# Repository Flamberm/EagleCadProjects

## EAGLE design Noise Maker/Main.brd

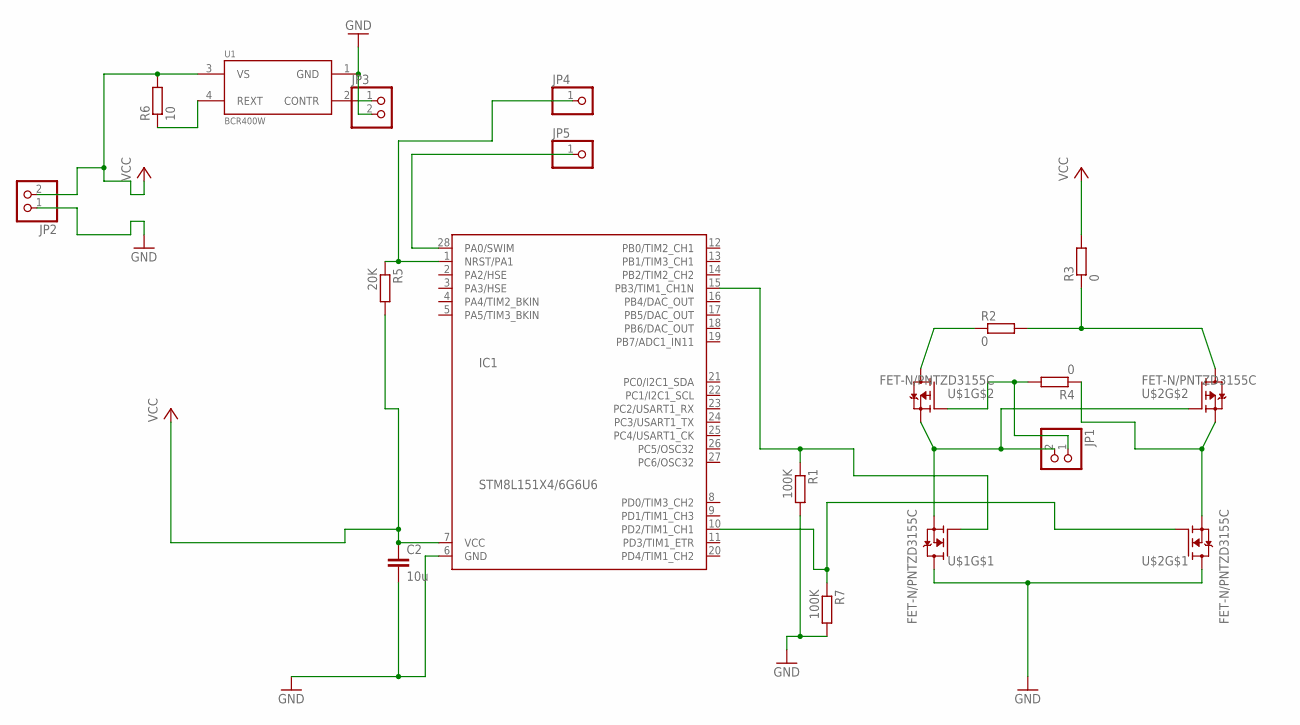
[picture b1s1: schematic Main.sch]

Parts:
C2: 10u; C0805
IC1: STM8L151X4/6G6U6; QFN28
JP1, JP2, JP3: PINHD-1X2; 1X02
JP4, JP5: PINHD-1X1; 1X01
R1, R7: 100K; R0805
R2, R3, R4: 0; R0805
R5: 20K; R0805
R6: 10; R0805
U1: BCR400W; SOT130P210X100-4N
U$1, U$2: FET-N/PNTZD3155C; SOT-563

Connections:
GND: C2.2, IC1.6 (GND), JP2.1, JP3.2, R1.2, R7.2, U1.1 (GND), U$1.6 (D), U$2.6 (D)
unnamed: R6.1, U1.4 (REXT)
unnamed: IC1.28 (PA0/SWIM), JP5.1
unnamed: IC1.1 (NRST/PA1), JP4.1, R5.1
unnamed: JP3.1, U1.2 (CONTR)
unnamed: R4.1, U$2.1 (S), U$2.4 (S)
unnamed: JP1.2, U$1.1 (S), U$1.4 (S), U$2.5 (G)
unnamed: IC1.10 (PD2/TIM1_CH1), R7.1, U$2.2 (G)
unnamed: R2.1, U$1.3 (D)
unnamed: R2.2, R3.1, U$2.3 (D)
unnamed: JP1.1, R4.2, U$1.5 (G)
unnamed: IC1.15 (PB3/TIM1_CH1N), R1.1, U$1.2 (G)
VCC: C2.1, IC1.7 (VCC), JP2.2, R3.2, R5.2, R6.2, U1.3 (VS)

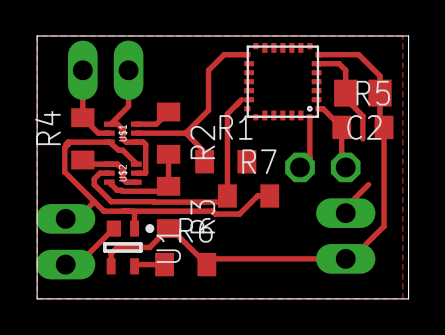
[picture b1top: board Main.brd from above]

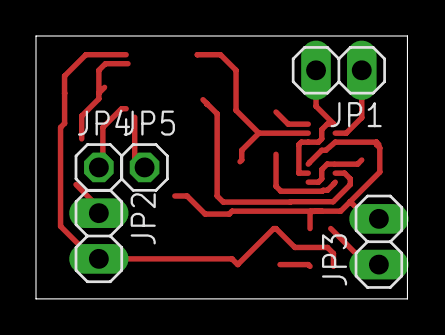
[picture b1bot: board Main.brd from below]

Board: 2 copper layers, 20.6 x 14.6 mm, 17 parts (5 on the bottom side), 13 nets.

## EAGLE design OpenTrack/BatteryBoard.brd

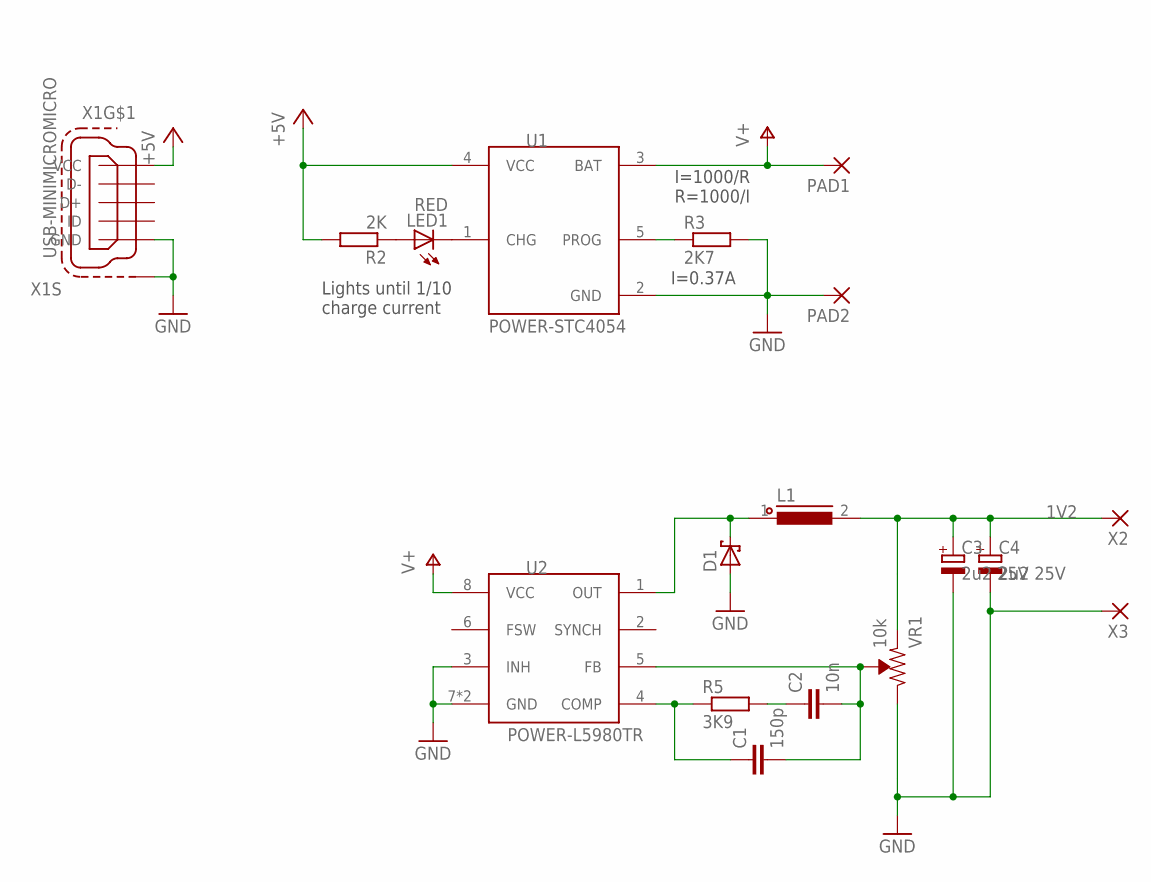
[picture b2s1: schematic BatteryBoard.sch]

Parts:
C1: 150p; CAP0805
C2: 10n; CAP0805
C3, C4: 2u2 25V; CAPMP3317X180
D1: DIODE-SH_SMA; DO214AC
L1: INDUCTORNL4532; INDM4232X320
LED1: RED; LED1206
PAD1, PAD2: WIREPAD-SMD2; PAD-1.27X2.54
R2: 2K; RESC2012X50
R3: 2K7; RESC2012X50
R5: 3K9; RESC2012X50
U1: POWER-STC4054; SOT95P280X145-5
U2: POWER-L5980TR; QFPN8
VR1: 10k; TRIMPOT-SMD-TC33X
X1: USB-MINIMICROMICRO; USB-B-MICRO-SMD
X2, X3: WIREPAD-SMD2; PAD-1.27X2.54

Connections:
1V2: C3.1 (+), C4.1 (+), L1.2, VR1.3 (CCW), X2.P$1
+5V: R2.2, U1.4 (VCC), X1.VBUS (VCC)
GND: C3.2 (-), C4.2 (-), D1.A, PAD2.P$1, R3.2, U1.2 (GND), U2.3 (INH), U2.7 (GND), U2.EXP (GND), VR1.1 (CW), X1.GND, X1.SHIELD1 (S1), X1.SHIELD2 (S1), X1.SHIELD3 (S1), X3.P$1
unnamed: LED1.C, U1.1 (CHG)
unnamed: LED1.A, R2.1
unnamed: D1.C, L1.1, U2.1 (OUT)
unnamed: R3.1, U1.5 (PROG)
unnamed: C1.2, C2.2, U2.5 (FB), VR1.2 (WIPER)
unnamed: C2.1, R5.2
unnamed: C1.1, R5.1, U2.4 (COMP)
V+: PAD1.P$1, U1.3 (BAT), U2.8 (VCC)

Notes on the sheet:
I=1000/R R=1000/I
I=0.37A
Lights until 1/10 charge current

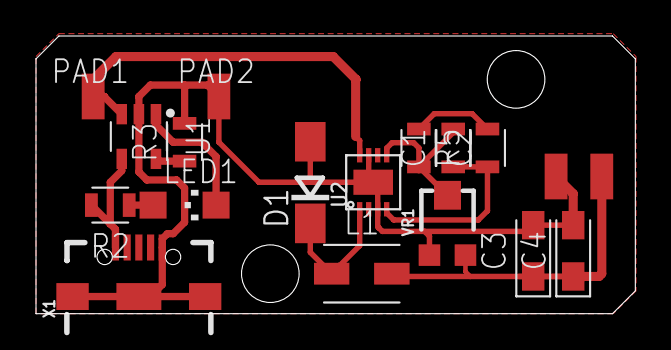
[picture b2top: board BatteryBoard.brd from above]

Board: 2 copper layers, 33.3 x 15.4 mm, 18 parts (0 on the bottom side), 11 nets.

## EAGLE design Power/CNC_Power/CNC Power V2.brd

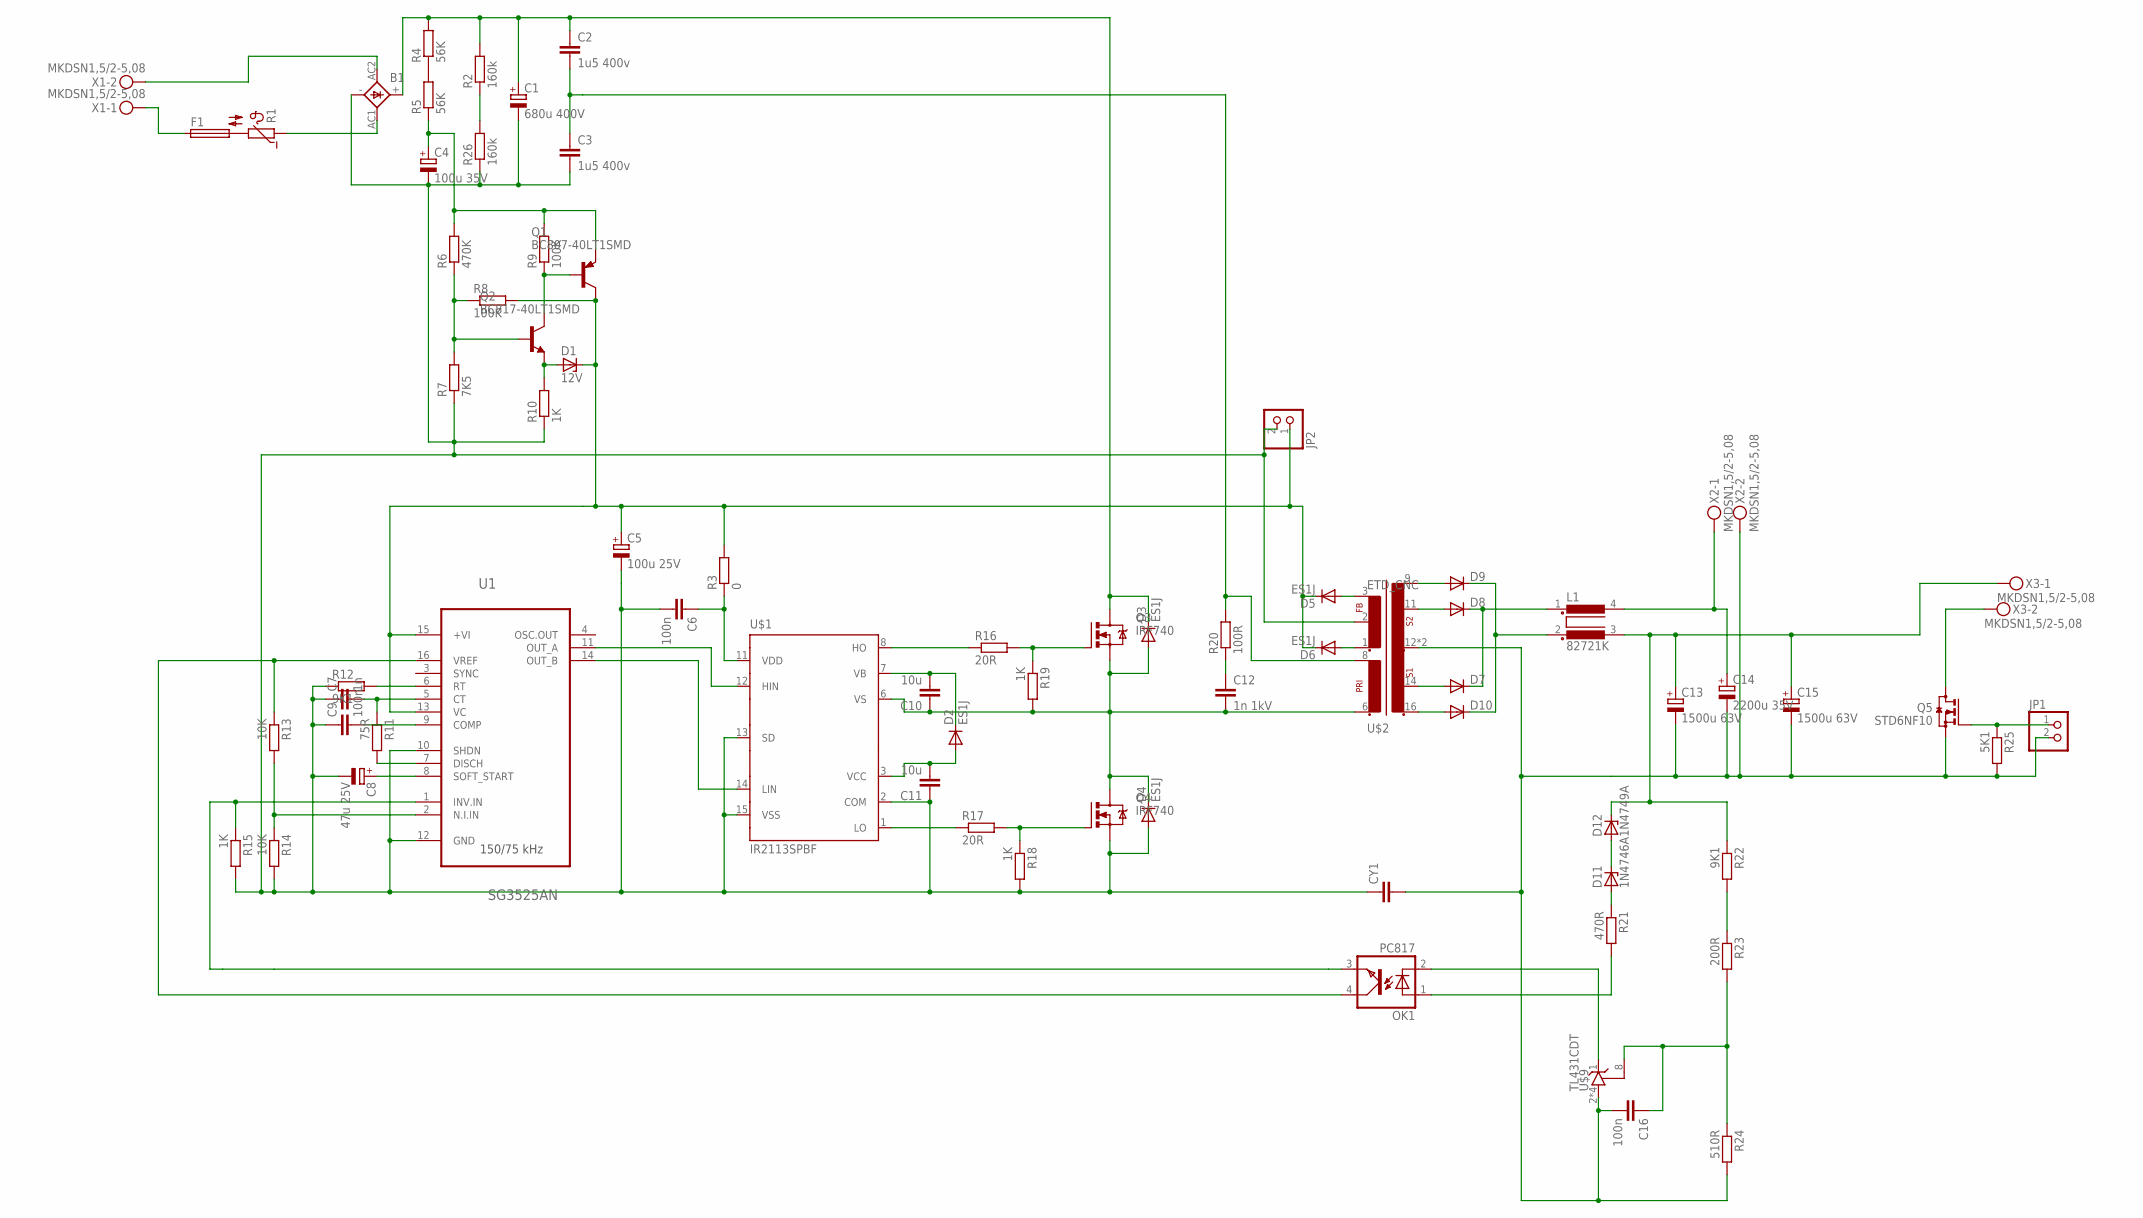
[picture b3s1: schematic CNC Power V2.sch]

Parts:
B1: KBL
C1: 680u 400V; EB35D
C2, C3: 1u5 400v; C225-074X268
C4: 100u 35V; E2,5-7
C5: 100u 25V; E2,5-7
C6, C9, C16: 100n; C0805
C7: 1n; C0805
C8: 47u 25V; E2,5-7
C10, C11: 10u; C0805
C12: 1n 1kV; C050-025X075
C13, C15: 1500u 63V; E7,5-18
C14: 2200u 35V; E7,5-18
CY1: CYYC10B4; YC10B4
D1: 12V; SOD80C
D2, D3, D4, D5, D6: ES1J; DO214AC
D7, D8, D9, D10: DIODE-DO220S; DO220S
D11: 1N4746A; DO41Z10
D12: 1N4749A; DO41Z10
F1: SH22,5
JP1, JP2: PINHD-1X2; 1X02
L1: 82721K
OK1: PC817; DIL04
Q1: BC807-40LT1SMD; SOT23-BEC
Q2: BC817-40LT1SMD; SOT23-BEC
Q3, Q4: IRF740; TO220BV
Q5: STD6NF10; DPAK
R1: B57164
R2, R26: 160k; 0207/10
R3: 0; R1206
R4, R5: 56K; 0617/17
R6: 470K; R0805
R7: 7K5; R0805
R8, R9: 100K; R0805
R10, R15, R18, R19: 1K; R0805
R11: 75R; R0805
R12, R22: 9K1; R0805
R13, R14: 10K; R0805
R16, R17: 20R; R1206
R20: 100R; 0617/17
R21: 470R; R0805
R23: 200R; R0805
R24: 510R; R0805
R25: 5K1; R0805
U1: SG3525AN; DIP254P762X510-16
U$1: IR2113SPBF; SO16W
U$2: ETD_CNC; ETD39_16PIN
U$9: TL431CDT; SO8
X1, X2, X3: MKDSN1,5/2-5,08

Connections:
12V: C5.+, D1.C, D5.C, D6.C, JP2.1, Q1.C, R3.2, R8.2, U1.13 (VC), U1.15 (+VI)
HV-0: B1.-, C1.-, C3.2, C4.-, C5.-, C6.2, C7.1, C8.-, C9.1, C11.1, CY1.1, D4.A, JP2.2, Q4.S, R7.1, R10.1, R12.1, R14.2, R15.2, R18.2, R26.1, U1.10 (SHDN), U1.12 (GND), U$1.2 (COM), U$1.13 (SD), U$1.15 (VSS), U$2.2 (F0)
HV-150: C2.2, C3.1, R20.2, U$2.8 (P-2)
HV-300: B1.+, C1.+, C2.1, D3.C, Q3.D, R2.2, R4.2
unnamed: B1.AC2 (AC1), X1.2
unnamed: F1.1, X1.1
unnamed: B1.AC1 (AC2), R1.1
unnamed: D7.A, U$2.14 (S1+24)
unnamed: R16.1, U$1.8 (HO)
unnamed: R17.1, U$1.1 (LO)
unnamed: Q3.G, R16.2, R19.1
unnamed: OK1.3 (EMIT), R15.1, U1.1 (INV.IN)
unnamed: R4.1, R5.2
unnamed: C4.+, Q1.E, R5.1, R6.2, R9.2
unnamed: Q2.B, R6.1, R7.2, R8.1
unnamed: Q1.B, Q2.C, R9.1
unnamed: C6.1, R3.1, U$1.11 (VDD)
unnamed: D1.A, Q2.E, R10.2
unnamed: C7.2, R11.1, U1.5 (CT)
unnamed: R11.2, U1.7 (DISCH)
unnamed: Q4.G, R17.2, R18.1
unnamed: U1.11 (OUT_A), U$1.12 (HIN)
unnamed: U1.14 (OUT_B), U$1.14 (LIN)
unnamed: R12.2, U1.6 (RT)
unnamed: C8.+, U1.8 (SOFT_START)
unnamed: C9.2, U1.9 (COMP)
unnamed: OK1.4 (COL), R13.1, U1.16 (VREF)
unnamed: R13.2, R14.1, U1.2 (N.I.IN)
unnamed: F1.2, R1.2
unnamed: D10.A, U$2.16 (S1+48)
unnamed: D8.A, U$2.11 (S-24)
unnamed: D6.A, U$2.1 (F+12)
unnamed: D5.A, U$2.3 (F-12)
unnamed: C12.1, R20.1
unnamed: D9.A, U$2.9 (S-48)
unnamed: D7.C, D8.C, L1.1
unnamed: D9.C, D10.C, L1.2 (3)
unnamed: C13.-, C14.-, C15.-, C16.2, CY1.2, JP1.2, Q5.S, R24.2, R25.2, U$2.12 (S-0), U$2.13 (S-0), U$9.2 (A), U$9.3 (A), U$9.6 (A), U$9.7 (A), X2.2
unnamed: C14.+, L1.4 (2), X2.1
unnamed: C13.+, C15.+, D12.C, L1.3 (4), R22.1, X3.1
unnamed: D11.C, D12.A
unnamed: D11.A, R21.1
unnamed: OK1.1 (A), R21.2
unnamed: OK1.2 (C), U$9.1 (C)
unnamed: C16.1, R23.2, R24.1, U$9.8 (R)
unnamed: R22.2, R23.1
unnamed: JP1.1, Q5.G, R25.1
unnamed: R2.1, R26.2
unnamed: Q5.D, X3.2
VB: C10.2, D2.C, U$1.7 (VB)
VCC: C11.2, D2.A, U$1.3 (VCC)
VS: C10.1, C12.2, D3.A, D4.C, Q3.S, Q4.D, R19.2, U$1.6 (VS), U$2.6 (P-1)

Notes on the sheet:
150/75 kHz

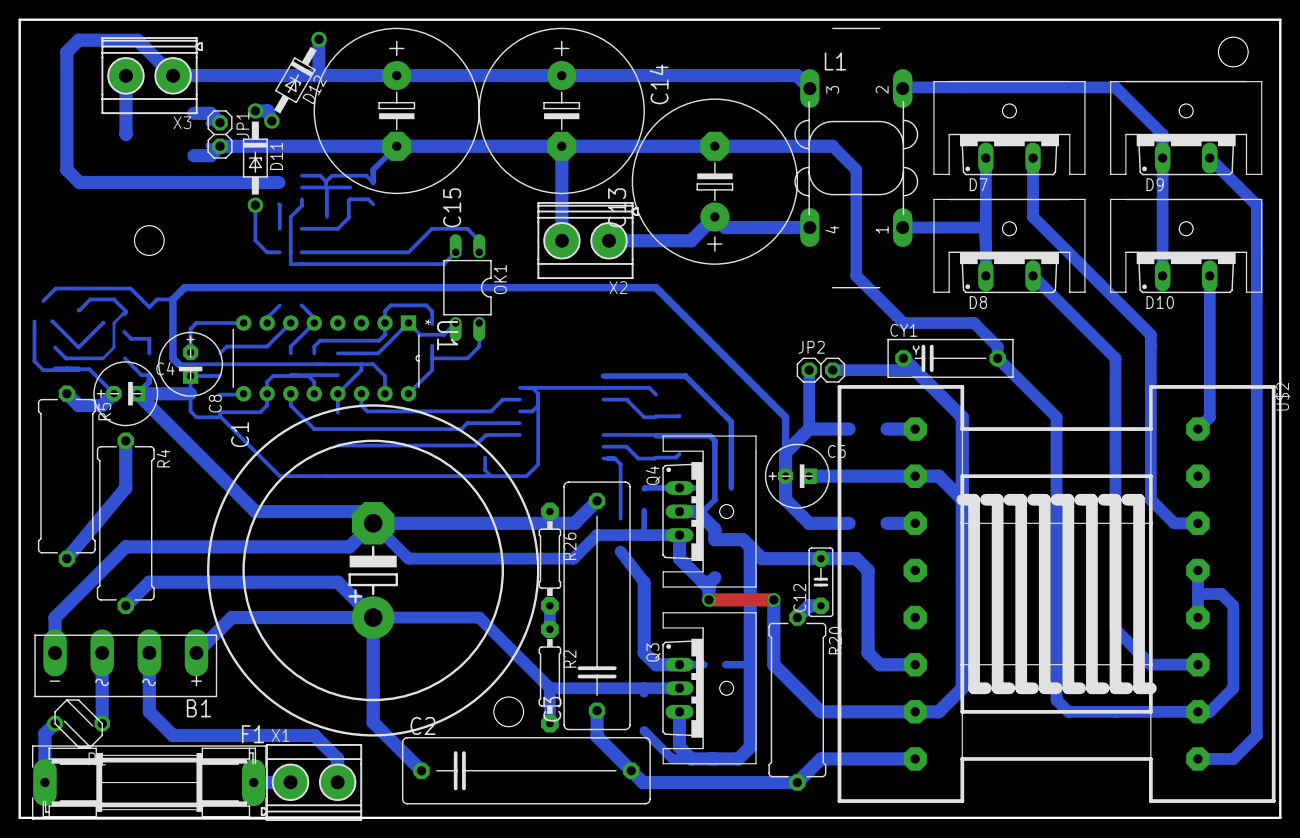
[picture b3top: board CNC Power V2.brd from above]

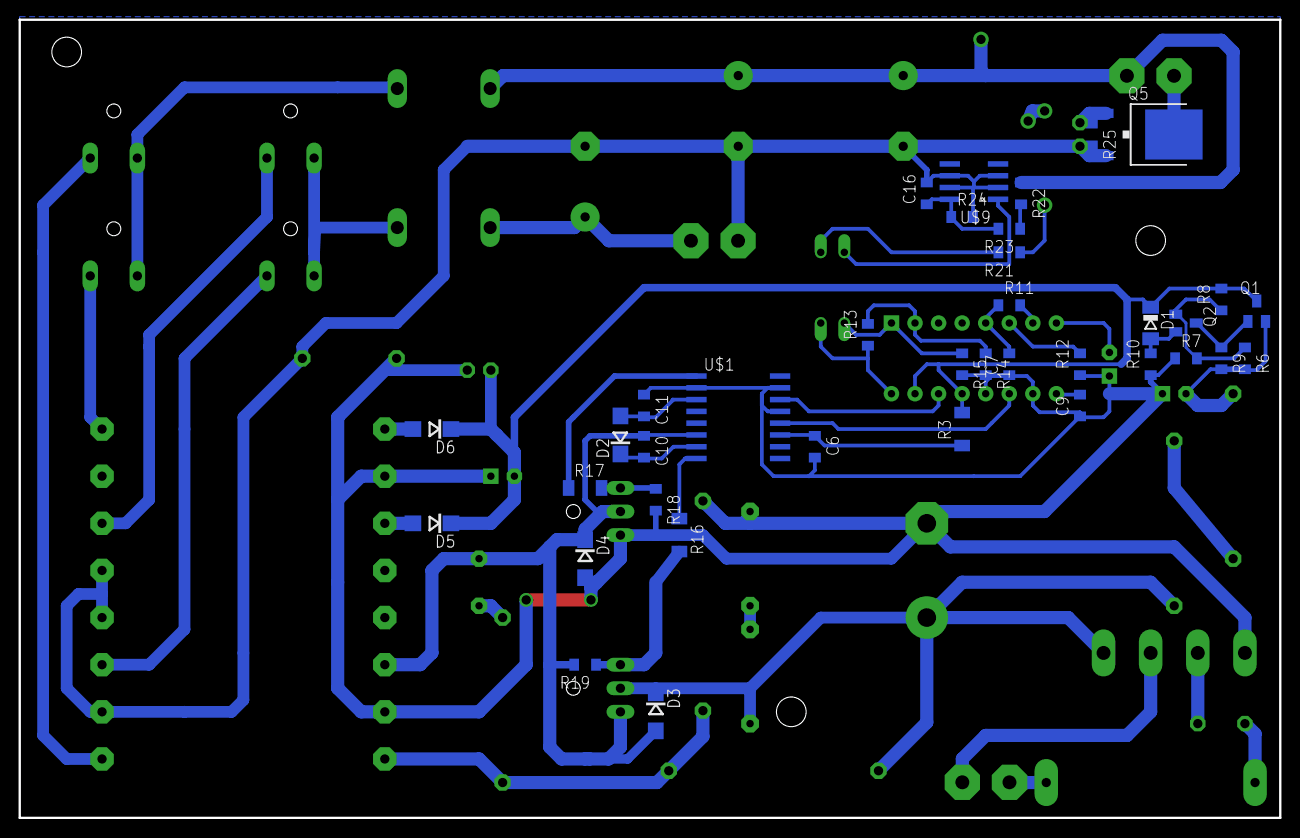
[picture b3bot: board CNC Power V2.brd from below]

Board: 2 copper layers, 135.9 x 86.0 mm, 79 parts (37 on the bottom side), 52 nets.

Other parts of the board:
U$3, U$4, U$5, U$6, U$7, U$8: SK95-3M3_HOLE

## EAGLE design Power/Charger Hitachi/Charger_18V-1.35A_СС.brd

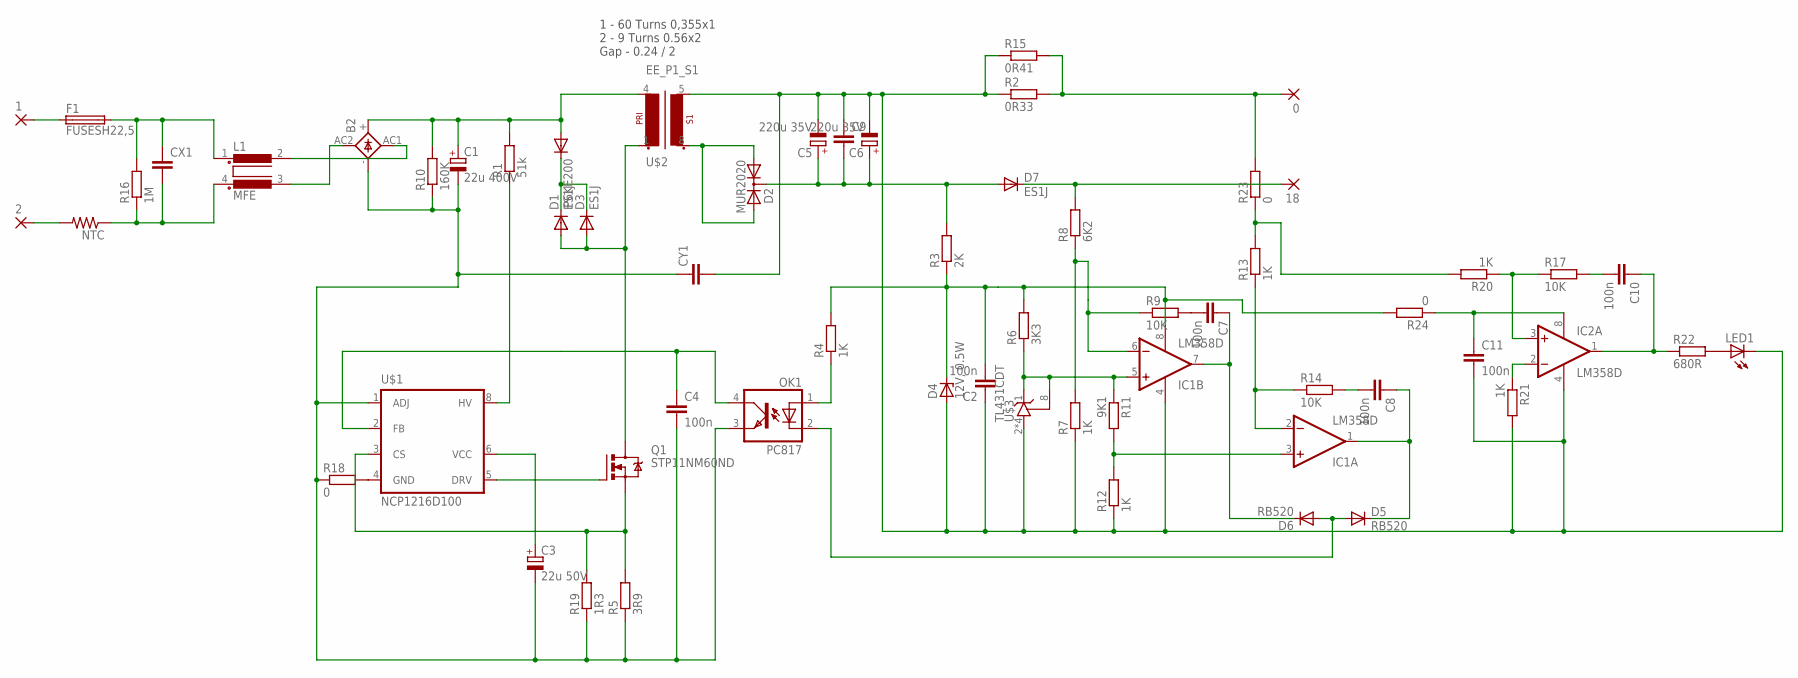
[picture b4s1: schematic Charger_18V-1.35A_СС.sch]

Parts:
0, 1, 2, 18: 3,81/1,4
B2: RS-4M
C1: 22u 400V; E7,5-18
C2, C4, C7, C8, C10, C11: 100n; C0805
C3: 22u 50V; E5-5
C5, C6: 220u 35V; E5-10,5
C9: C-EU050-025X075; C050-025X075
CX1: CXXC22B7; XC22B7
CY1: CYYC10B4; YC10B4
D1, D3, D7: ES1J; DO-214AC
D2: MUR2020; TO220ABS
D4: 12V, 0.5W; SOD80C
D5, D6: RB520; SOD523
F1: FUSESH22,5; SH22,5
IC1, IC2: LM358D; SO08
L1: MFE
LED1: LED5MM
NTC: R-US_0207/7; 0207/7
OK1: PC817; DIL04
P6KE200: DIODE-SMB; SMB
Q1: STP11NM60ND; TO220BV
R1: 51k; SQP-5
R2: 0R33; 0411/15
R3: 2K; R1206
R4, R7, R12, R13, R20, R21: 1K; R0603
R5: 3R9; 0309/12
R6: 3K3; R1206
R8: 6K2; R0805
R9, R14, R17: 10K; R0805
R10: 160K; 0204/7
R11: 9K1; R1206
R15: 0R41; 0411/15
R16: 1M; 0207/12
R18, R23, R24: 0; R1206
R19: 1R3; 0309/12
R22: 680R; R0805
U$1: NCP1216D100; SOP8
U$2: EE_P1_S1; EE25_P1_S1
U$3: TL431CDT; SO8

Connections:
unnamed: 2.1, NTC.2
unnamed: CX1.1, F1.2, L1.1, R16.2
unnamed: B2.AC2 (AC1), L1.3 (4)
unnamed: D2.A1, D2.A2, U$2.8 (S1-1)
unnamed: C4.1, OK1.4 (COL), U$1.2 (FB)
unnamed: B2.+, C1.+, P6KE200.A, R1.2, R10.2, U$2.4 (P1-2)
unnamed: D1.C, D3.C, P6KE200.C
unnamed: D1.A, D3.A, Q1.D, U$2.1 (P1-1)
unnamed: 0.1, R2.2, R15.2, R23.2
unnamed: R1.1, U$1.8 (HV)
unnamed: Q1.G, U$1.5 (DRV)
unnamed: Q1.S, R5.2, R19.2, U$1.3 (CS)
unnamed: C2.2, D4.C, IC1.8 (V+), R3.1, R4.2, R6.2, R24.2
unnamed: C3.+, U$1.6 (VCC)
unnamed: OK1.1 (A), R4.1
unnamed: B2.-, C1.-, C3.-, C4.2, CY1.1, OK1.3 (EMIT), R5.1, R10.1, R18.1, R19.1, U$1.1 (ADJ)
unnamed: IC1.3 (+IN), R11.2, R12.2
unnamed: C2.1, C5.-, C6.-, C9.1, C11.2, CY1.2, D4.A, IC1.4 (V-), IC2.4 (V-), LED1.K (C), R2.1, R7.1, R12.1, R15.1, R21.2, U$2.5 (S1-2), U$3.2 (A), U$3.3 (A), U$3.6 (A), U$3.7 (A)
unnamed: C5.+, C6.+, C9.2, D2.C, D7.A, R3.2
unnamed: IC1.5 (+IN), R6.1, R11.1, U$3.1 (C), U$3.8 (R)
unnamed: IC1.6 (-IN), R7.2, R8.1, R9.1
unnamed: C7.2, R9.2
unnamed: C7.1, D6.C, IC1.7 (OUT)
unnamed: IC1.2 (-IN), R13.1, R14.1
unnamed: C8.2, R14.2
unnamed: C8.1, D5.C, IC1.1 (OUT)
unnamed: D5.A, D6.A, OK1.2 (C)
unnamed: C10.1, IC2.1 (OUT), R22.1
unnamed: R18.2, U$1.4 (GND)
unnamed: B2.AC1 (AC2), L1.2
unnamed: CX1.2, L1.4 (3), NTC.1, R16.1
unnamed: 1.1, F1.1
unnamed: C10.2, R17.2
unnamed: IC2.3 (+IN), R17.1, R20.1
unnamed: IC2.2 (-IN), R21.1
unnamed: C11.1, IC2.8 (V+), R24.1
unnamed: 18.1, D7.C, R8.2
unnamed: LED1.A, R22.2
unnamed: R13.2, R20.2, R23.1

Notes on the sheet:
1 - 60 Turns 0,355x1 2 - 9 Turns 0.56x2 Gap - 0.24 / 2

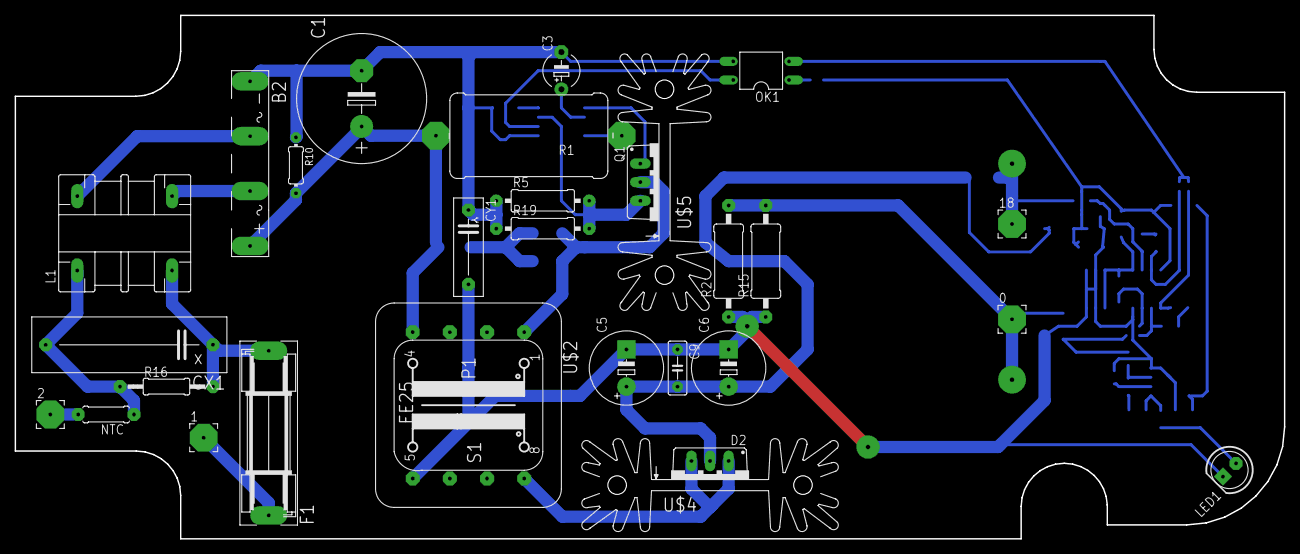
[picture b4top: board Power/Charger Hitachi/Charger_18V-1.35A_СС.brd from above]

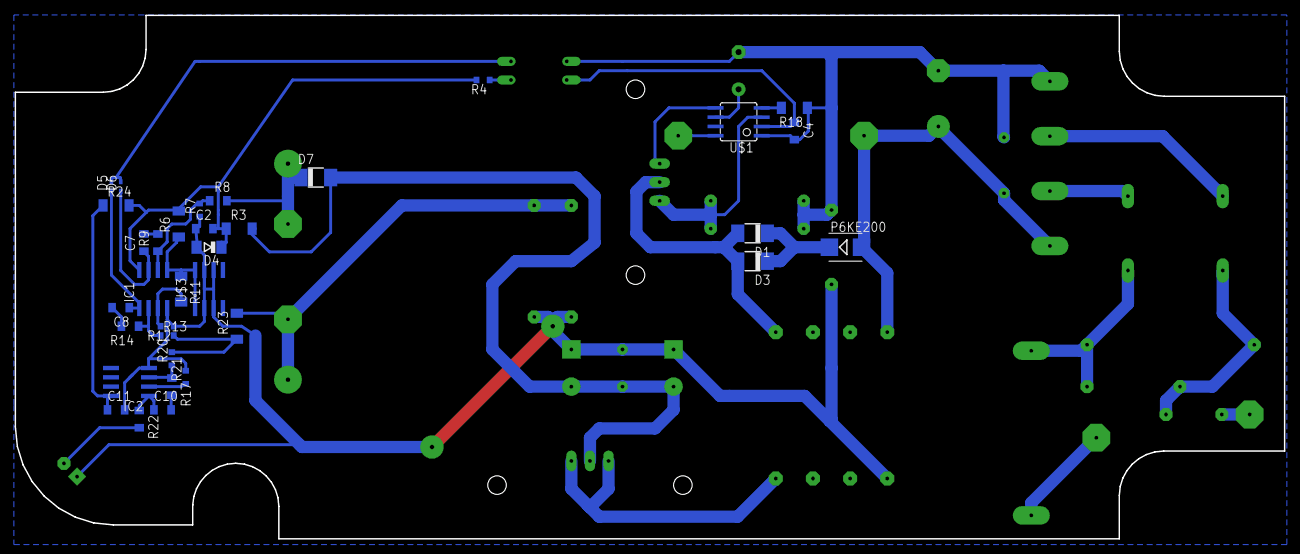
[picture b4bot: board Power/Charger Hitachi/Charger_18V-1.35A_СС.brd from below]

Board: 2 copper layers, 173.5 x 71.5 mm, 63 parts (34 on the bottom side), 39 nets.

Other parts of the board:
U$4, U$5: SK104

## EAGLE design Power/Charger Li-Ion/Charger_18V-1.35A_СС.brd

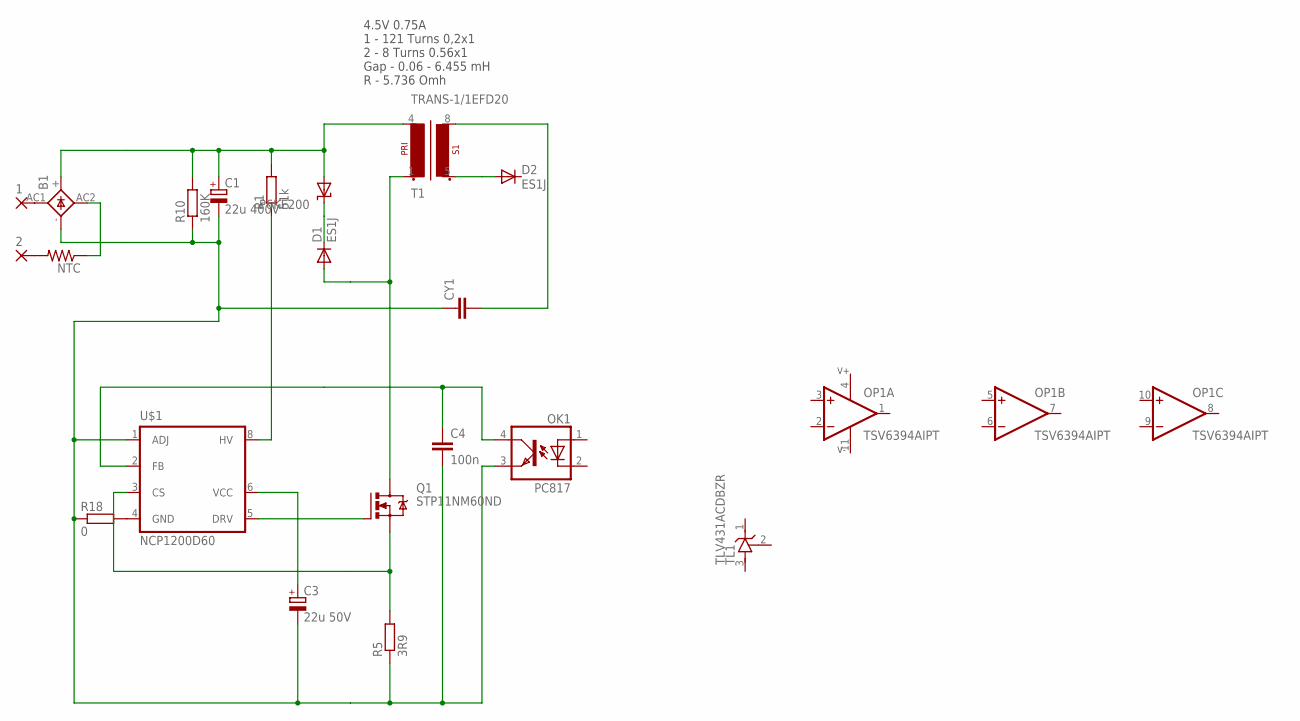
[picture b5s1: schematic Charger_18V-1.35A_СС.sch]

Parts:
1, 2: 3,81/1,4
B1: BRIDGEDBS; DBS
C1: 22u 400V; E7,5-18
C3: 22u 50V; E5-5
C4: 100n; C0805
CY1: CYYC10B4; YC10B4
D1, D2: ES1J; DO-214AC
NTC: R-US_0207/7; 0207/7
OK1: PC817; DIL04
OP1: TSV6394AIPT; TSSOP14
P6KE200: SUPRESSORDO-204AC; DO15-12
Q1: STP11NM60ND; TO220BV
R1: 51k; SQP-5
R5: 3R9; 0309/12
R10: 160K; 0204/7
R18: 0; R1206
T1: TRANS-1/1EFD20; EFD20_8PIN
TL1: TLV431ACDBZR; SOT23
U$1: NCP1200D60; DIP08

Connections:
unnamed: 2.1, NTC.2
unnamed: D2.A, T1.5 (S1-1)
unnamed: 1.1, B1.AC1
unnamed: B1.AC2, NTC.1
unnamed: C4.1, OK1.4 (COL), U$1.2 (FB)
unnamed: B1.+, C1.+, P6KE200.A, R1.2, R10.2, T1.4 (P1-2)
unnamed: D1.C, P6KE200.C
unnamed: D1.A, Q1.D, T1.1 (P1-1)
unnamed: R1.1, U$1.8 (HV)
unnamed: Q1.G, U$1.5 (DRV)
unnamed: Q1.S, R5.2, U$1.3 (CS)
unnamed: C3.+, U$1.6 (VCC)
unnamed: B1.-, C1.-, C3.-, C4.2, CY1.1, OK1.3 (EMIT), R5.1, R10.1, R18.1, U$1.1 (ADJ)
unnamed: CY1.2, T1.8 (S1-2)
unnamed: R18.2, U$1.4 (GND)
V+: OP1.4 (V+)
V-: OP1.11 (V-)

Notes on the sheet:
4.5V 0.75A 1 - 121 Turns 0,2x1 2 - 8 Turns 0.56x1 Gap - 0.06 - 6.455 mH R - 5.736 Omh

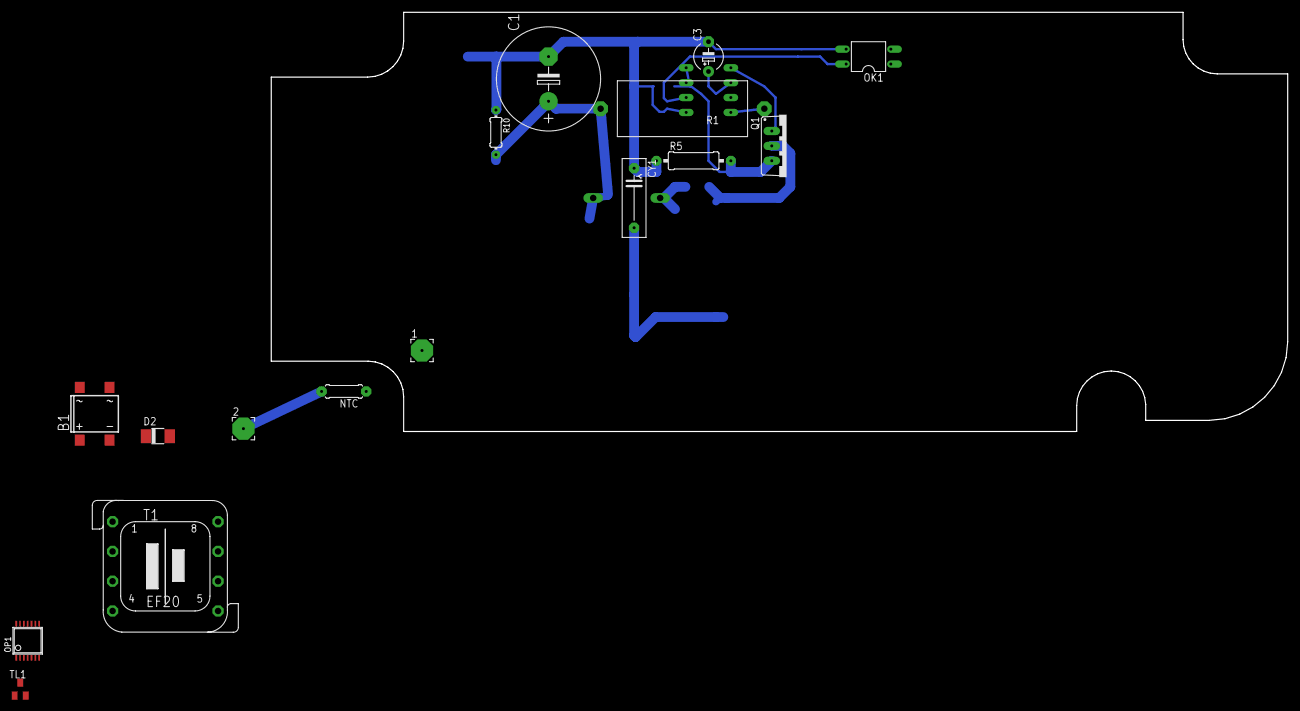
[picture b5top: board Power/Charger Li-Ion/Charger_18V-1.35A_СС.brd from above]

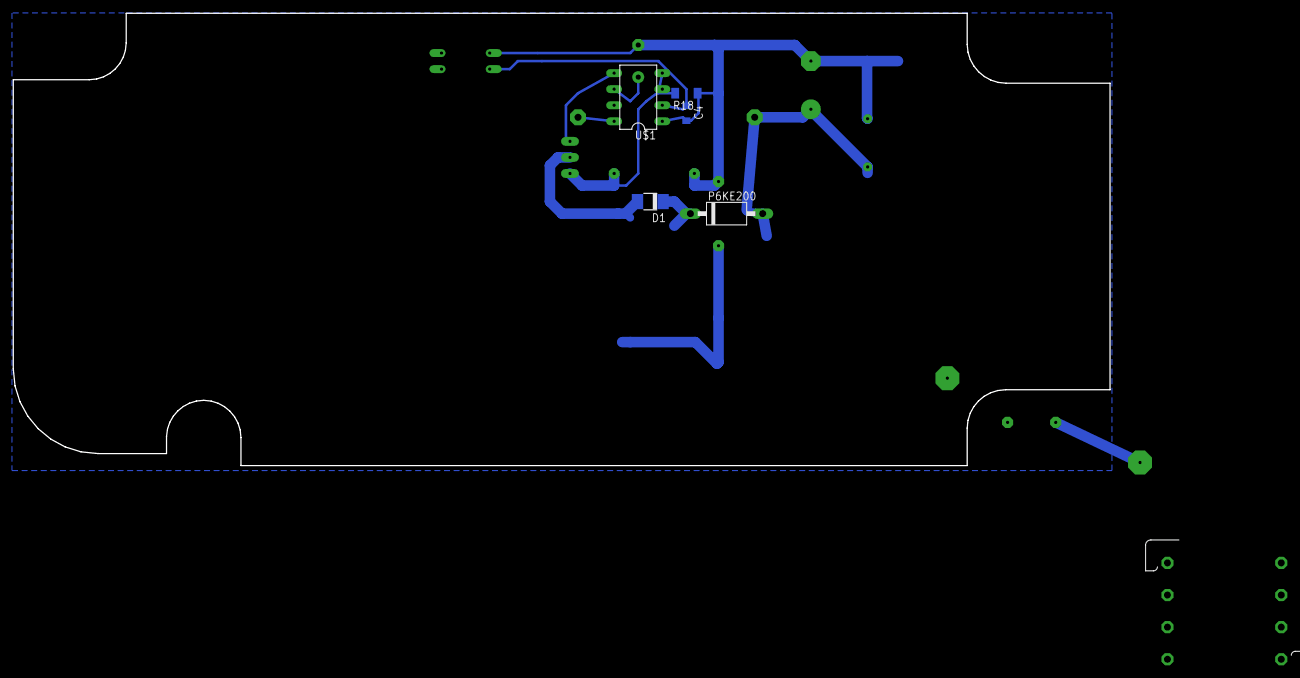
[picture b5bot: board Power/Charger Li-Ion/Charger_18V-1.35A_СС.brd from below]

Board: 2 copper layers, 173.5 x 71.5 mm, 21 parts (5 on the bottom side), 15 nets.

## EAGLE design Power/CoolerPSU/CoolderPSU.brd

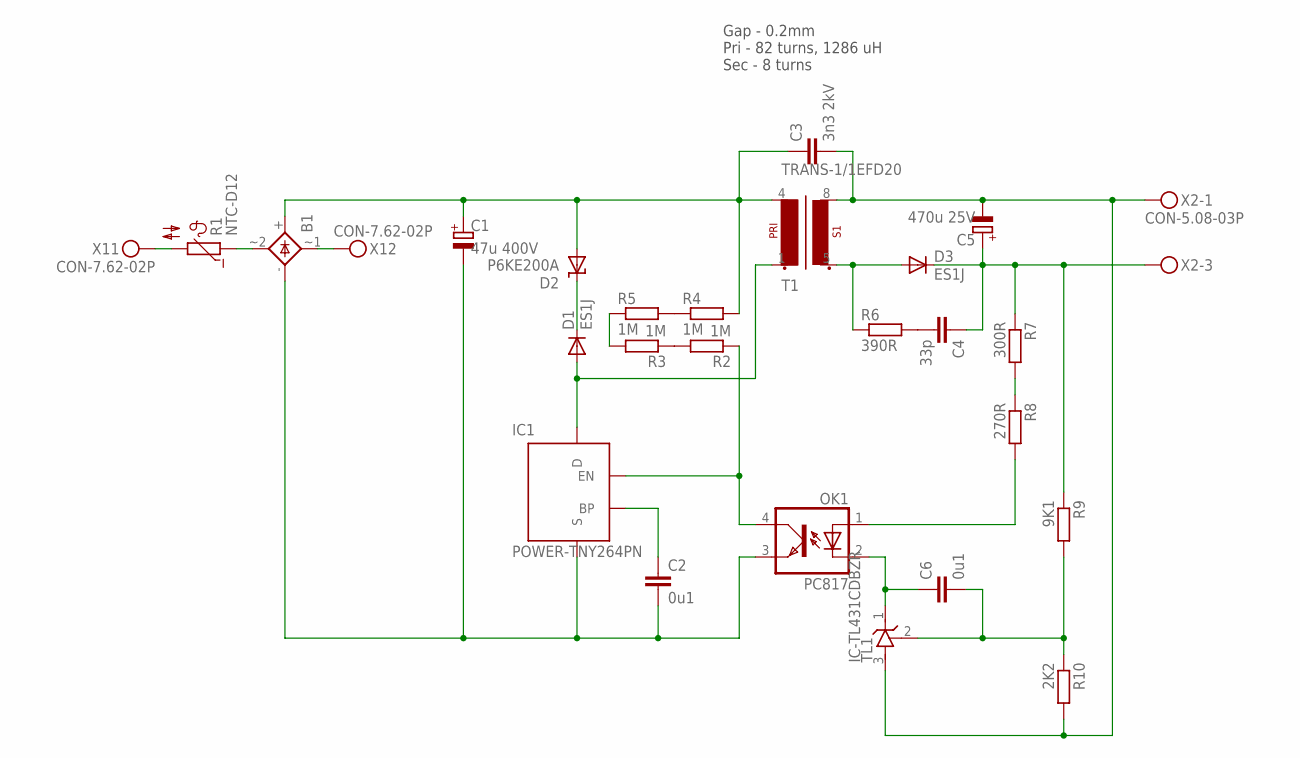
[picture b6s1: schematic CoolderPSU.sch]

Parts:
B1: RECTIFIERSOIC-8; SOIC-4
C1: 47u 400V; E7,5-16-32-HORIZ
C2, C6: 0u1; C0805
C3: 3n3 2kV; C050-024X044
C4: 33p; C0805
C5: 470u 25V; E2,5-7
D1, D3: ES1J; DO214AC
D2: P6KE200A; DO15-12
IC1: POWER-TNY264PN; DIP-8B
OK1: PC817; DIL04
R1: NTC-D12
R2, R3, R4, R5: 1M; R1206
R6: 390R; R1206
R7: 300R; R1206
R8: 270R; R1206
R9: 9K1; R1206
R10: 2K2; R1206
T1: TRANS-1/1EFD20; EFD20_8PIN
TL1: IC-TL431CDBZR; SOT23
X1: CON-7.62-02P; KF25C-7.62-02P-13
X2: CON-5.08-03P; MKDSN1,5/3-5,08

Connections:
unnamed: R1.2, X1.P$1
unnamed: B1.~2 (AC2), R1.1
unnamed: B1.~1 (AC1), X1.P$2
unnamed: B1.+, C1.+, C3.1, D2.A, R4.2, T1.4 (P1-2)
unnamed: B1.-, C1.-, C2.2, IC1.2 (S), IC1.3 (S), IC1.7 (S), IC1.8 (S), OK1.3 (EMIT)
unnamed: D1.A, IC1.5 (D), T1.1 (P1-1)
unnamed: D1.C, D2.C
unnamed: R2.2, R3.1
unnamed: R4.1, R5.2
unnamed: IC1.4 (EN), OK1.4 (COL), R2.1
unnamed: R3.2, R5.1
unnamed: C2.1, IC1.1 (BP)
unnamed: C3.2, C5.-, R10.2, T1.8 (S1-2), TL1.3 (A), X2.1
unnamed: D3.A, R6.1, T1.5 (S1-1)
unnamed: C4.2, R6.2
unnamed: C4.1, C5.+, D3.C, R7.1, R9.1, X2.3
unnamed: C6.1, OK1.2 (C), TL1.1 (C)
unnamed: R7.2, R8.1
unnamed: OK1.1 (A), R8.2
unnamed: C6.2, R9.2, R10.1, TL1.2 (R)

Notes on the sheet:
Gap - 0.2mm Pri - 82 turns, 1286 uH Sec - 8 turns

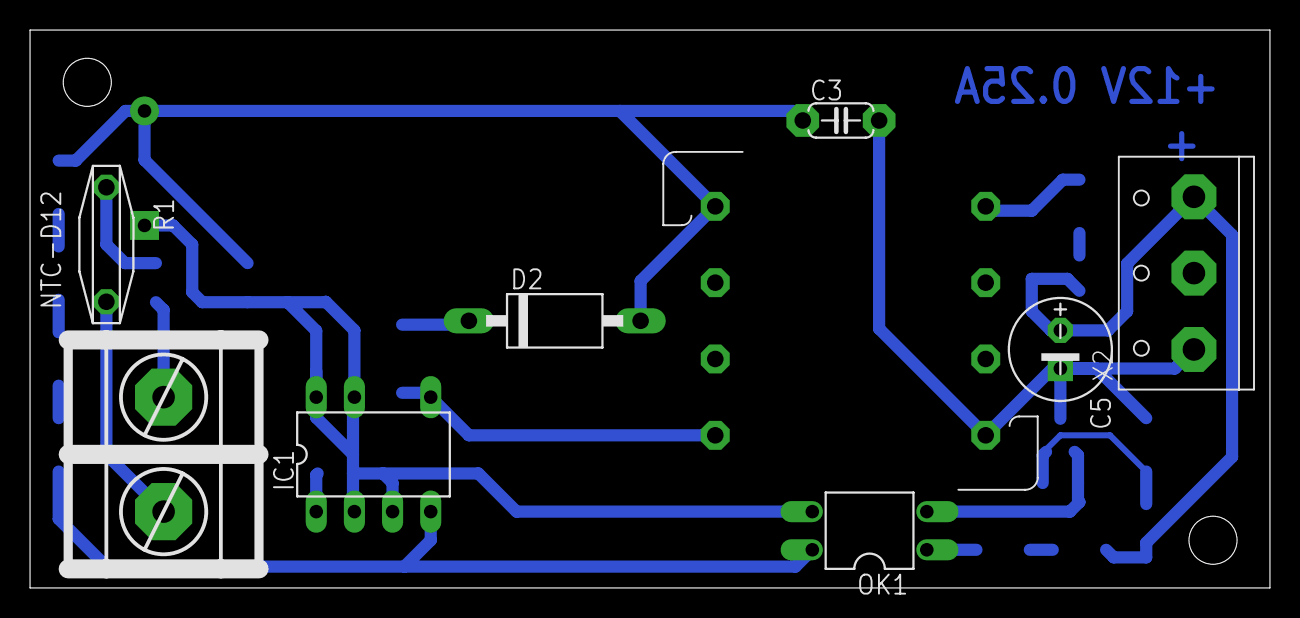
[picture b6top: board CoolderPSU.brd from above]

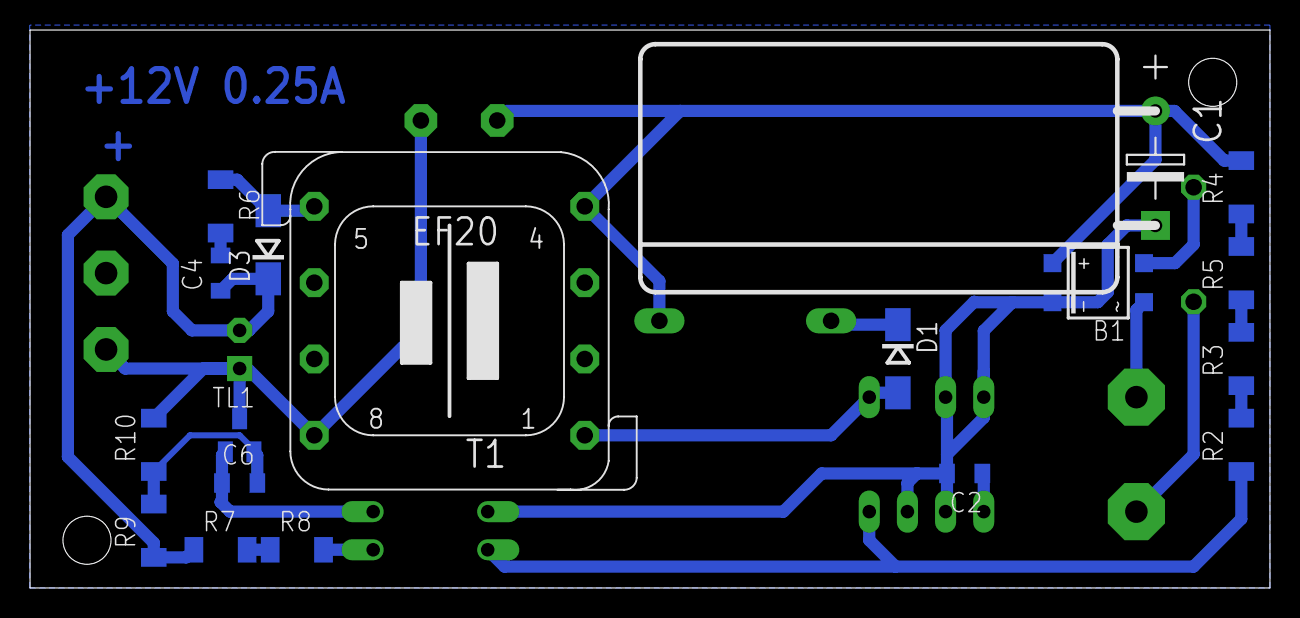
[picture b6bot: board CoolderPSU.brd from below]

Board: 2 copper layers, 82.5 x 37.1 mm, 26 parts (18 on the bottom side), 20 nets.

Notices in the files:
parts and their libraries:
SparkFun-Resistors: Licensing: Creative Commons ShareAlike 4.0 International - https://creativecommons.org/licenses/by-sa/4.0
